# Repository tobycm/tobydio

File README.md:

# tobydio - a breakout board for developing with DAC and ADC ICs

A semi-assembled board to develop with DAC and ADC from chip makers like TI. Featuring a line in and line out 3.5mm headphone jack to receive and output sound signal, pin headers to interface with microcontrollers, and awesome art. 

Cost: $33.87

This is my fourth pcb ever. I developed this during my pixeldust ysws where I wanted to incorporate some audio system in my project and this is one way for me to test subsystems. I learned how to find and source parts from suppliers like DigiKey, LCSC. I also learned how to get symbols, footprints, and models to help my development process.

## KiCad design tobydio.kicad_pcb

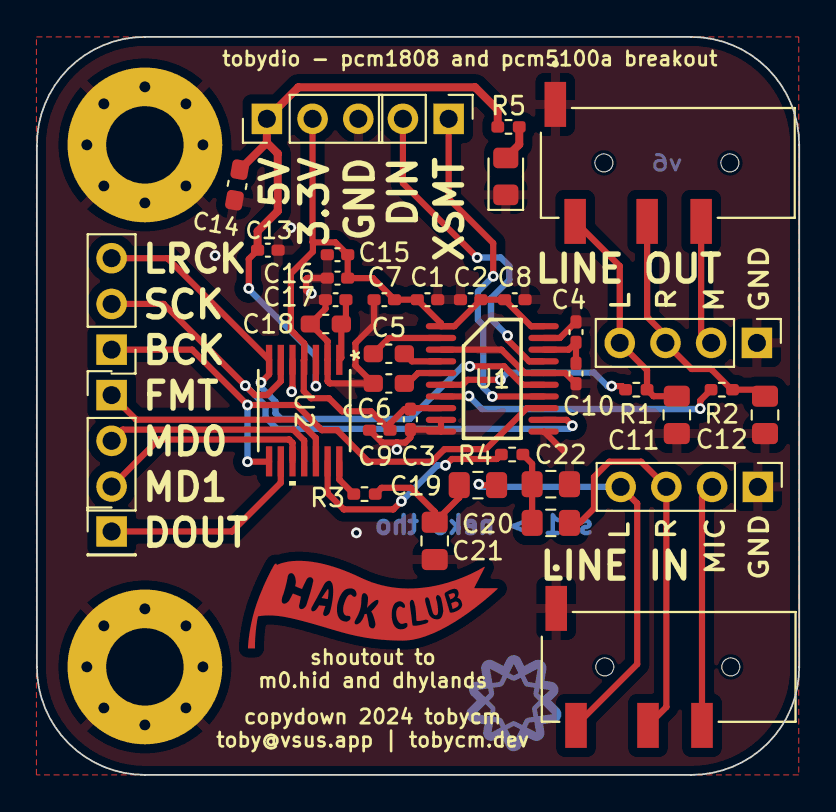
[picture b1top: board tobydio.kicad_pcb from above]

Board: 2 copper layers, 42.4 x 41.0 mm, 41 parts (0 on the bottom side), 30 nets.

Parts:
C1, C2, C3, C4, C13, C15, C17: 0.1uF; C_0402_1005Metric_Pad0.74x0.62mm_HandSolder
C5, C6: 2.2uF; C_0603_1608Metric_Pad1.08x0.95mm_HandSolder
C7, C8, C9, C10, C16: 10uF; C_0402_1005Metric_Pad0.74x0.62mm_HandSolder
C11, C12, C21, C22: 2.2nF; C_0805_2012Metric_Pad1.18x1.45mm_HandSolder
C14, C18: 10uF; C_0603_1608Metric_Pad1.08x0.95mm_HandSolder
C19, C20: 1uF; C_0805_2012Metric_Pad1.18x1.45mm_HandSolder
D1: LED; LED_0805_2012Metric_Pad1.15x1.40mm_HandSolder
H1, H2: MountingHole_Pad; MountingHole_4.3mm_M4_Pad_Via
J1: Conn_01x02_Pin; PinHeader_1x02_P2.54mm_Vertical
J2, J8: PJ-320D-A; HRO_PJ-320D-A
J3, J7: Conn_01x04_Pin; PinHeader_1x04_P2.54mm_Vertical
J5: Conn_01x01_Pin; PinHeader_1x01_P2.54mm_Vertical
J6, J9, J10: Conn_01x03_Pin; PinHeader_1x03_P2.54mm_Vertical
R1, R2, R3, R4: 470; R_0402_1005Metric_Pad0.72x0.64mm_HandSolder
R5: 220; R_0402_1005Metric_Pad0.72x0.64mm_HandSolder
U1: PCM5100APWR; PW0020A
U2: PCM1808PWR; PW14

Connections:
+3.3V: C1.1, C2.1, C3.1, C7.1, C8.1, C9.1, C15.1, C16.1, J10.2, U1.1 (CPVDD), U1.8 (AVDD), U1.20 (DVDD), U2.4 (VDD)
+5V: C13.1, C14.1, J10.1, R5.1, U2.3 (VCC)
BCK: J6.1, U1.13 (BCK), U2.8 (BCK)
GND: C1.2, C2.2, C3.2, C4.2, C6.2, C7.2, C8.2, C9.2, C10.2, C11.2, C12.2, C13.2, C14.2, C15.2, C16.2, C17.2, C18.2, C21.2, C22.2, D1.1 (K), H1.1, H2.1, J2.1, J3.1, J7.1, J8.1, J10.3, U1.3 (CPGND), U1.9 (AGND), U1.10 (DEMP), U1.11 (FLT), U1.16 (FMT), U1.19 (DGND), U2.2 (AGND), U2.5 (DGND)
LRCK: J6.3, U1.15 (LRCK), U2.7 (LRCK)
unnamed: C19.1, C21.1, R3.2
unnamed: C20.1, C22.1, R4.2
unnamed: D1.2 (A), R5.2
unnamed: J1.1, U1.14 (DIN)
unnamed: J1.2, U1.17 (XSMT)
unnamed: J2.2, J3.2
unnamed: C12.1, J2.3, J3.3, R2.2
unnamed: C11.1, J2.4, J3.4, R1.2
unnamed: J5.1, U2.9 (DOUT)
unnamed: J7.2, J8.2
unnamed: C20.2, J7.3, J8.3
unnamed: C19.2, J7.4, J8.4
unnamed: J9.1, U2.12 (FMT)
unnamed: J9.2, U2.11 (MD1)
unnamed: J9.3, U2.10 (MD0)
unnamed: C5.2, U1.4 (CAPM)
unnamed: C5.1, U1.2 (CAPP)
unnamed: C4.1, C10.1, U1.18 (LDOO)
unnamed: R1.1, U1.6 (OUTL)
unnamed: R2.1, U1.7 (OUTR)
unnamed: C6.1, U1.5 (VNEG)
unnamed: R4.1, U2.13 (VINL)
unnamed: R3.1, U2.14 (VINR)
unnamed: C17.1, C18.1, U2.1 (VREF)
SCK: J6.2, U1.12 (SCK), U2.6 (SCKI)

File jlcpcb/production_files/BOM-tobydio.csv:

Comment,Designator,Footprint,LCSC,Quantity
PCM5100APWR,U1,PW0020A,C131154,1
0.1uF,"C1,C13,C15,C17,C2,C3,C4",C_0402_1005Metric_Pad0.74x0.62mm_HandSolder,C1525,7
10uF,"C10,C16,C7,C8,C9",C_0402_1005Metric_Pad0.74x0.62mm_HandSolder,C15525,5
PJ-320D-A,"J2,J8",HRO_PJ-320D-A,C19189088,2
10uF,"C14,C18",C_0603_1608Metric_Pad1.08x0.95mm_HandSolder,C19702,2
LED,D1,LED_0805_2012Metric_Pad1.15x1.40mm_HandSolder,C2297,1
2.2uF,"C5,C6",C_0603_1608Metric_Pad1.08x0.95mm_HandSolder,C23630,2
220,R5,R_0402_1005Metric_Pad0.72x0.64mm_HandSolder,C25091,1
470,"R1,R2,R3,R4",R_0402_1005Metric_Pad0.72x0.64mm_HandSolder,C25117,4
2.2nF,"C11,C12,C21,C22",C_0805_2012Metric_Pad1.18x1.45mm_HandSolder,C28260,4
1uF,"C19,C20",C_0805_2012Metric_Pad1.18x1.45mm_HandSolder,C28323,2
PCM1808PWR,U2,PW14,C55513,1

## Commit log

2025-05-01 add board and gerber files
